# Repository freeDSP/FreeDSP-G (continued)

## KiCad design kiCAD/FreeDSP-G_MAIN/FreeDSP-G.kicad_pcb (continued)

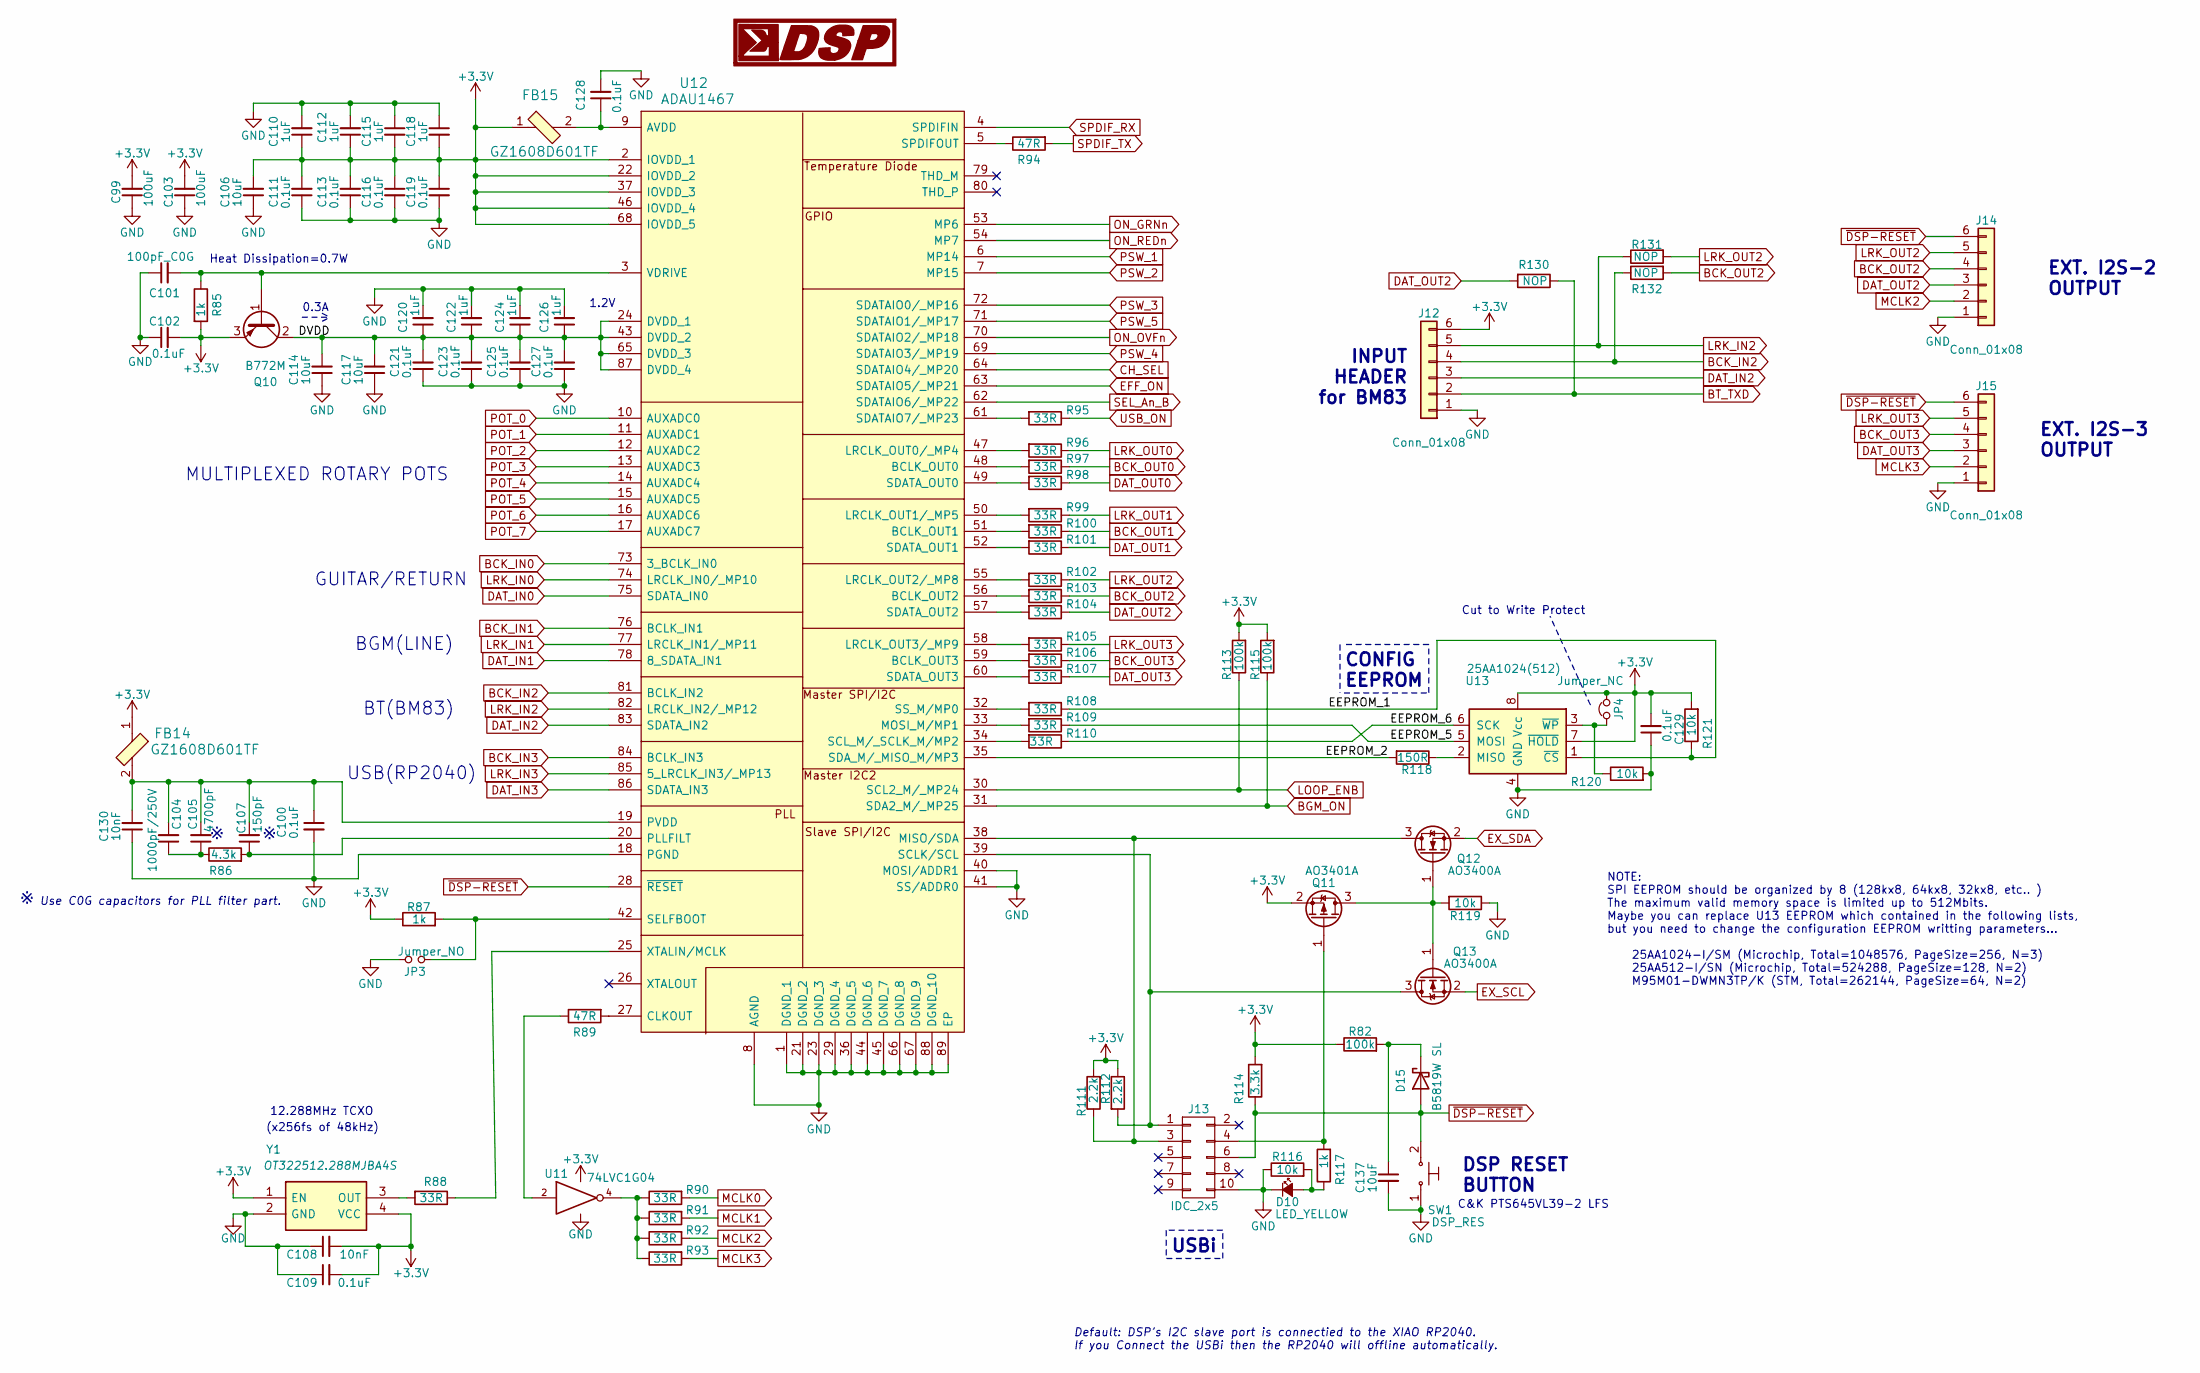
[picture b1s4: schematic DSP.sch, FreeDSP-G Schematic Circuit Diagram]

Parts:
C99, C103: 100uF; C_1206_3216Metric
C100, C102, C109, C111, C113, C116, C119, C121, C123, C125, C127, C128, C129: 0.1uF; C_0603_1608Metric_Pad1.08x0.95mm_HandSolder
C101: 100pF_C0G; C_0603_1608Metric_Pad1.08x0.95mm_HandSolder
C104: 1000pF/250V; C_0805_2012Metric
C105: 4700pF; C_0805_2012Metric
C106, C114, C117, C137: 10uF; C_0805_2012Metric
C107: 150pF; C_0805_2012Metric
C108, C130: 10nF; C_0603_1608Metric_Pad1.08x0.95mm_HandSolder
C110, C112, C115, C118, C120, C122, C124, C126: 1uF; C_0603_1608Metric_Pad1.08x0.95mm_HandSolder
D10: LED_YELLOW; LED_0603_1608Metric_Castellated
D15: B5819W SL; D_SOD-123
FB14, FB15: GZ1608D601TF; L_0603_1608Metric_Pad1.05x0.95mm_HandSolder; MPN BLM18AG601SN1D; Digi-Key_PN 490-1014-1-ND
J12, J14, J15: Conn_01x08; PinHeader_1x06_P2.54mm_Vertical
J13: IDC_2x5; IDC-Header_2x05_P2.54mm_Vertical
JP3: Jumper_NO; PinHeader_1x02_P2.54mm_Vertical
JP4: Jumper_NC; SolderJumper-2_P1.3mm_Bridged_RoundedPad1.0x1.5mm
Q10: B772M; TO-252-2
Q11: AO3401A; SOT-23; Manufacturer_Part_Number DMG3415U-7; Mouser Part Number 621-DMG3415U-7
Q12, Q13: AO3400A; SOT-23
R82, R113, R115: 100k; R_0603_1608Metric_Pad0.98x0.95mm_HandSolder
R85, R87, R117: 1k; R_0603_1608Metric_Pad0.98x0.95mm_HandSolder
R86: 4.3k; R_0603_1608Metric_Pad0.98x0.95mm_HandSolder
R88, R90, R91, R92, R93, R95, R96, R97, R98, R99, R100, R101, R102, R103, R104, R105, R106, R107, R108, R109, R110: 33R; R_0603_1608Metric_Pad0.98x0.95mm_HandSolder
R89, R94: 47R; R_0603_1608Metric_Pad0.98x0.95mm_HandSolder
R111, R112: 2.2k; R_0603_1608Metric_Pad0.98x0.95mm_HandSolder
R114: 3.3k; R_0603_1608Metric_Pad0.98x0.95mm_HandSolder
R116, R119, R120, R121: 10k; R_0603_1608Metric_Pad0.98x0.95mm_HandSolder
R118: 150R; R_0603_1608Metric_Pad0.98x0.95mm_HandSolder
R130, R131, R132: NOP; R_0603_1608Metric_Pad0.98x0.95mm_HandSolder
SW1: DSP_RES; SW_Tactile_SPST_Angled_PTS645Vx83-2LFS
U11: 74LVC1G04; SOT-23-5_HandSoldering
U12: ADAU1467; ADAU1467WBCPZ300
U13: 25AA1024(512); SOIC-8_3.9x4.9mm_P1.27mm
Y1: OT322512.288MJBA4S; Crystal_SMD_TXC_7M-4pin_3.2x2.5mm_HandSoldering; Manufacturer_Part_Number KC7050K50.0000C1GE00
Z1: LOGO; SigmaDSP-LogoSmall

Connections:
+3V3: C99.2, C102.2, C103.2, C106.2, C108.2, C109.2, C110.1, C111.2, C112.1, C113.2, C115.2, C116.1, C118.2, C119.1, C129.2, FB14.1, FB15.1, J12.6, JP4.2, Q10.3 (E), Q11.2 (S), R82.1, R85.2, R87.1, R111.2, R112.1, R113.2, R114.2, R115.2, R121.2, U11.5 (VCC), U12.2 (IOVDD_1), U12.22 (IOVDD_2), U12.37 (IOVDD_3), U12.46 (IOVDD_4), U12.68 (IOVDD_5), U13.7 (~HOLD), U13.8 (Vcc), Y1.1 (EN), Y1.4 (VCC); also elsewhere on the board
/DSP/DVDD: C114.2, C117.2, C120.1, C121.2, C122.1, C123.2, C124.1, C125.2, C126.1, C127.2, Q10.2 (C), U12.24 (DVDD_1), U12.43 (DVDD_2), U12.65 (DVDD_3), U12.87 (DVDD_4)
/DSP/EEPROM_1: R108.1, R121.1, U13.1 (~CS)
/DSP/EEPROM_2: R118.2, U12.35 (SDA_M/_MISO_M/MP3)
/DSP/EEPROM_5: R109.1, U13.5 (MOSI)
/DSP/EEPROM_6: R110.1, U13.6 (SCK)
BCK_IN0: U12.73 (3_BCLK_IN0); also elsewhere on the board
BCK_IN1: U12.76 (BCLK_IN1); also elsewhere on the board
BCK_IN2: J12.4, R132.1, U12.81 (BCLK_IN2); also elsewhere on the board
BCK_IN3: U12.84 (BCLK_IN3); also elsewhere on the board
BCK_OUT0: R97.1; also elsewhere on the board
BCK_OUT1: R100.1; also elsewhere on the board
BCK_OUT2: J14.4, R103.1, R132.2
BCK_OUT3: J15.4, R106.1
BGM_ON: R115.1, U12.31 (SDA2_M/_MP25); also elsewhere on the board
BT_TXD: J12.2, R130.1; also elsewhere on the board
CH_SEL: U12.64 (SDATAIO4/_MP20); also elsewhere on the board
DAT_IN0: U12.75 (SDATA_IN0); also elsewhere on the board
DAT_IN1: U12.78 (8_SDATA_IN1); also elsewhere on the board
DAT_IN2: J12.3, U12.83 (SDATA_IN2); also elsewhere on the board
DAT_IN3: U12.86 (SDATA_IN3); also elsewhere on the board
DAT_OUT0: R98.1; also elsewhere on the board
DAT_OUT1: R101.1; also elsewhere on the board
DAT_OUT2: J14.3, R104.1, R130.2
DAT_OUT3: J15.3, R107.1
EFF_ON: U12.63 (SDATAIO5/_MP21); also elsewhere on the board
EX_SCL: Q13.2 (S); also elsewhere on the board
EX_SDA: Q12.2 (S); also elsewhere on the board
GND: C99.1, C100.2, C101.1, C102.1, C103.1, C106.1, C108.1, C109.1, C110.2, C111.1, C112.2, C113.1, C114.1, C115.1, C116.2, C117.1, C118.1, C119.2, C120.2, C121.1, C122.2, C123.1, C124.2, C125.1, C126.2, C127.1, C128.2, C129.1, C130.1, C137.2, D10.1 (K), J12.1, J13.10, J14.1, J15.1, JP3.1, R116.1, R119.1, R120.2, SW1.1, U11.3 (GND), U12.1 (DGND_1), U12.8 (AGND), U12.18 (PGND), U12.21 (DGND_2), U12.23 (DGND_3), U12.29 (DGND_4), U12.36 (DGND_5), U12.40 (MOSI/ADDR1), U12.41 (SS/ADDR0), U12.44 (DGND_6), U12.45 (DGND_7), U12.66 (DGND_8), U12.67 (DGND_9), U12.88 (DGND_10), U12.89 (EP), U13.4 (GND), Y1.2 (GND); also elsewhere on the board
LOOP_ENB: R113.1, U12.30 (SCL2_M/_MP24); also elsewhere on the board
LRK_IN0: U12.74 (LRCLK_IN0/_MP10); also elsewhere on the board
LRK_IN1: U12.77 (LRCLK_IN1/_MP11); also elsewhere on the board
LRK_IN2: J12.5, R131.1, U12.82 (LRCLK_IN2/_MP12); also elsewhere on the board
LRK_IN3: U12.85 (5_LRCLK_IN3/_MP13); also elsewhere on the board
LRK_OUT0: R96.1; also elsewhere on the board
LRK_OUT1: R99.1; also elsewhere on the board
LRK_OUT2: J14.5, R102.1, R131.2
LRK_OUT3: J15.5, R105.1
MCLK0: R90.2; also elsewhere on the board
MCLK1: R91.2; also elsewhere on the board
MCLK2: J14.2, R92.2; also elsewhere on the board
MCLK3: J15.2, R93.2; also elsewhere on the board
unnamed: C100.1, C104.2, C105.2, C107.2, C130.2, FB14.2, U12.19 (PVDD)
unnamed: C101.2, Q10.1 (B), R85.1, U12.3 (VDRIVE)
unnamed: C104.1, C105.1, R86.1
unnamed: C107.1, R86.2, U12.20 (PLLFILT)
unnamed: C128.1, FB15.2, U12.9 (AVDD)
unnamed: C137.1, D15.1 (K), R82.2
unnamed: D10.2 (A), R116.2, R117.1
unnamed: J13.1, Q13.3 (D), R112.2, U12.39 (SCLK/SCL)
unnamed: J13.3, Q12.3 (D), R111.1, U12.38 (MISO/SDA)
unnamed: J13.4, Q11.1 (G), R117.2
unnamed: JP3.2, R87.2, U12.42 (SELFBOOT)
unnamed: JP4.1, R120.1, U13.3 (~WP)
unnamed: Q11.3 (D), Q12.1 (G), Q13.1 (G), R119.2
unnamed: R88.1, U12.25 (XTALIN/MCLK)
unnamed: R88.2, Y1.3 (OUT)
unnamed: R89.1, U11.2
unnamed: R89.2, U12.27 (CLKOUT)
unnamed: R90.1, R91.1, R92.1, R93.1, U11.4
unnamed: R94.1, U12.5 (SPDIFOUT)
unnamed: R95.2, U12.61 (SDATAIO7/_MP23)
unnamed: R96.2, U12.47 (LRCLK_OUT0/_MP4)
unnamed: R97.2, U12.48 (BCLK_OUT0)
unnamed: R98.2, U12.49 (SDATA_OUT0)
unnamed: R99.2, U12.50 (LRCLK_OUT1/_MP5)
unnamed: R100.2, U12.51 (BCLK_OUT1)
unnamed: R101.2, U12.52 (SDATA_OUT1)
unnamed: R102.2, U12.55 (LRCLK_OUT2/_MP8)
unnamed: R103.2, U12.56 (BCLK_OUT2)
unnamed: R104.2, U12.57 (SDATA_OUT2)
unnamed: R105.2, U12.58 (LRCLK_OUT3/_MP9)
unnamed: R106.2, U12.59 (BCLK_OUT3)
unnamed: R107.2, U12.60 (SDATA_OUT3)
unnamed: R108.2, U12.32 (SS_M/MP0)
unnamed: R109.2, U12.33 (MOSI_M/MP1)
unnamed: R110.2, U12.34 (SCL_M/_SCLK_M/MP2)
unnamed: R118.1, U13.2 (MISO)
ON_GRNn: U12.53 (MP6); also elsewhere on the board
ON_OVFn: U12.70 (SDATAIO2/_MP18); also elsewhere on the board
ON_REDn: U12.54 (MP7); also elsewhere on the board
POT_0: U12.10 (AUXADC0); also elsewhere on the board
POT_1: U12.11 (AUXADC1); also elsewhere on the board
POT_2: U12.12 (AUXADC2); also elsewhere on the board
POT_3: U12.13 (AUXADC3); also elsewhere on the board
POT_4: U12.14 (AUXADC4); also elsewhere on the board
POT_5: U12.15 (AUXADC5); also elsewhere on the board
POT_6: U12.16 (AUXADC6); also elsewhere on the board
POT_7: U12.17 (AUXADC7); also elsewhere on the board
PSW_1: U12.6 (MP14); also elsewhere on the board
PSW_2: U12.7 (MP15); also elsewhere on the board
PSW_3: U12.72 (SDATAIO0/_MP16); also elsewhere on the board
PSW_4: U12.69 (SDATAIO3/_MP19); also elsewhere on the board
PSW_5: U12.71 (SDATAIO1/_MP17); also elsewhere on the board
SEL_An_B: U12.62 (SDATAIO6/_MP22); also elsewhere on the board
SPDIF_RX: U12.4 (SPDIFIN); also elsewhere on the board
SPDIF_TX: R94.2; also elsewhere on the board
USB_ON: R95.1; also elsewhere on the board
~DSP-RESET: D15.2 (A), J13.6, J14.6, J15.6, R114.1, SW1.2, U12.28 (~RESET)

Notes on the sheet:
USBi
12.288MHz TCXO
USB(RP2040)
GUITAR/RETURN
MULTIPLEXED ROTARY POTS
BGM(LINE)
(x256fs of 48kHz)
NOTE: SPI EEPROM should be organized by 8 (128kx8, 64kx8, 32kx8, etc.. ) The maximum valid memory space is limited up to 512Mbits. Maybe you can replace U13 EEPROM which contained in the following lists, but you need to change the configuration EEPROM writting parameters… 25AA1024-I/SM (Microchip, 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
Default: DSP’s I2C slave port is connectied to the XIAO RP2040. If you Connect the USBi then the RP2040 will offline automatically.
0.3A
1.2V
Heat Dissipation=0.7W
DSP RESET BUTTON
C&K PTS645VL39-2 LFS
BT(BM83)
Cut to Write Protect
CONFIG EEPROM
Use C0G capacitors for PLL filter part.
INPUT HEADER for BM83
EXT. I2S-2 OUTPUT
EXT. I2S-3 OUTPUT

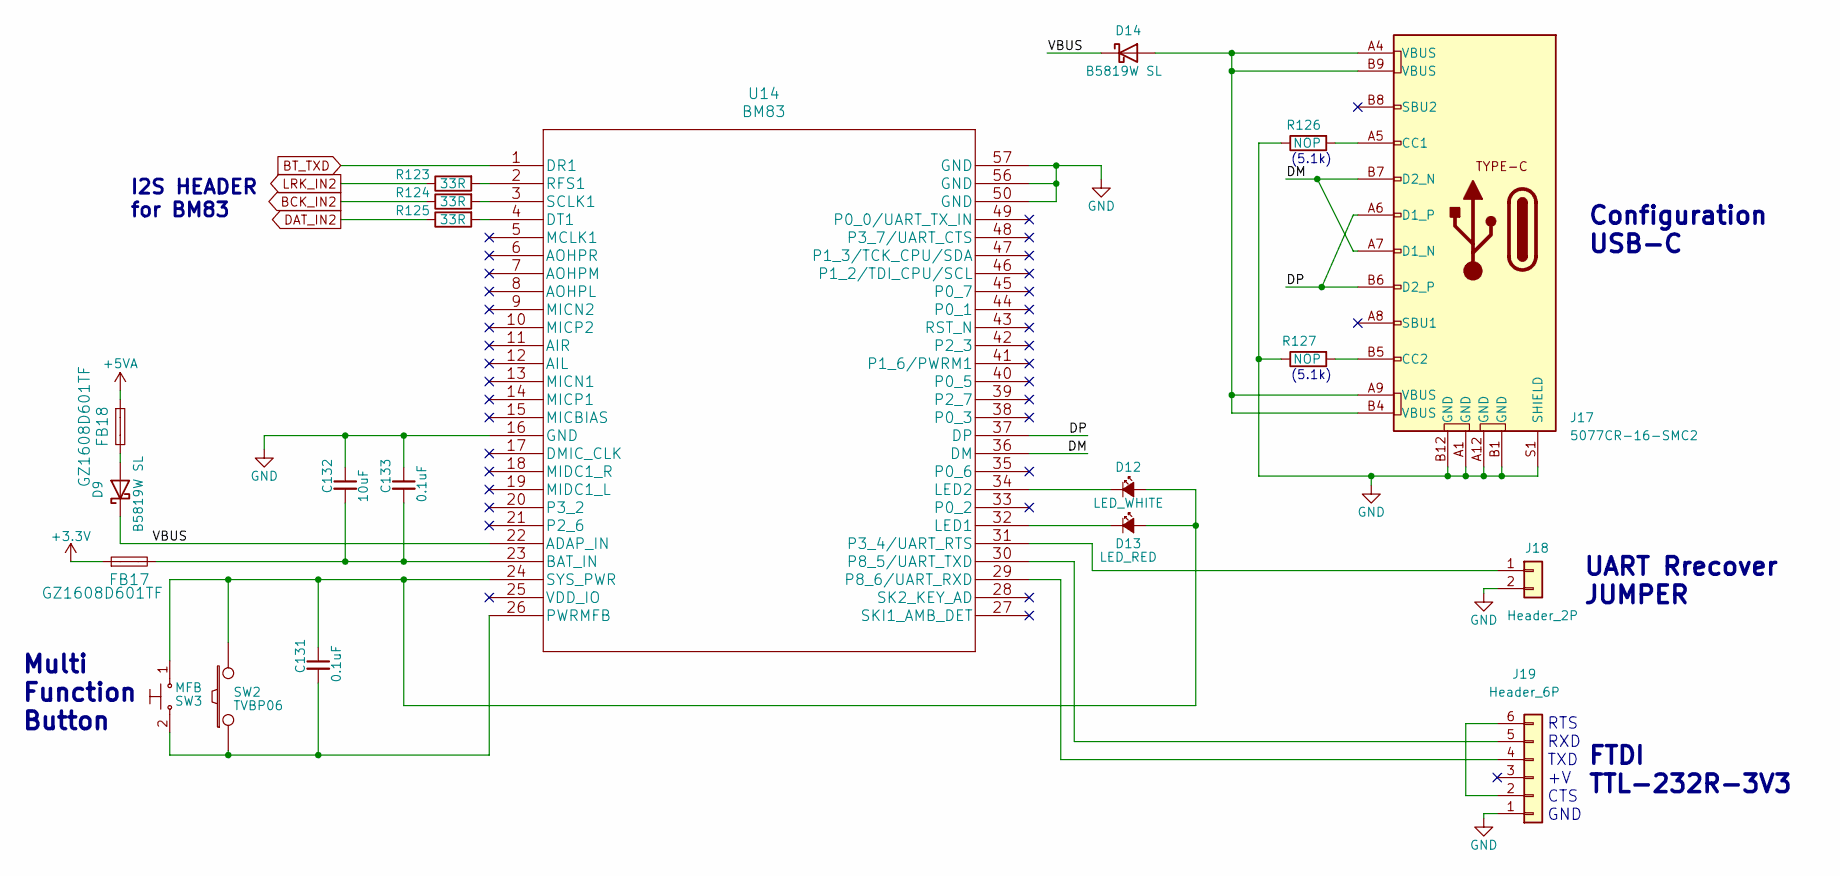
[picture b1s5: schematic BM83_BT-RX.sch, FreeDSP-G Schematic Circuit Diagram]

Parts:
C131, C133: 0.1uF; C_0603_1608Metric_Pad1.08x0.95mm_HandSolder
C132: 10uF; C_0805_2012Metric
D9, D14: B5819W SL; D_SOD-123
D12: LED_WHITE; LED_0603_1608Metric_Castellated
D13: LED_RED; LED_0603_1608Metric_Castellated
FB17, FB18: GZ1608D601TF; L_0603_1608Metric_Pad1.05x0.95mm_HandSolder; MPN BLM18AG601SN1D; Digi-Key_PN 490-1014-1-ND
J17: 5077CR-16-SMC2; USB-C_5077CR-16-SMC2-BK-TR
J18: Header_2P; PinHeader_1x02_P2.54mm_Vertical
J19: Header_6P; PinHeader_1x06_P2.54mm_Vertical
R123, R124, R125: 33R; R_0603_1608Metric_Pad0.98x0.95mm_HandSolder
R126, R127: NOP; R_0603_1608Metric_Pad0.98x0.95mm_HandSolder
SW2: TVBP06; MJTP1250
SW3: MFB; SW_Tactile_SPST_Angled_PTS645Vx83-2LFS
U14: BM83; BM83_MCH

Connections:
+3V3: FB17.1; also elsewhere on the board
+5VA: FB18.1; also elsewhere on the board
/BM83_BT-RX/DM: J17.A7 (D1_N), J17.B7 (D2_N), U14.36 (DM)
/BM83_BT-RX/DP: J17.A6 (D1_P), J17.B6 (D2_P), U14.37 (DP)
/BM83_BT-RX/VBUS: D9.1 (K), D14.1 (K), U14.22 (ADAP_IN)
BCK_IN2: R124.1; also elsewhere on the board
BT_TXD: U14.1 (DR1); also elsewhere on the board
DAT_IN2: R125.1; also elsewhere on the board
GND: C132.1, C133.1, J17.A1 (GND), J17.A12 (GND), J17.B1 (GND), J17.B12 (GND), J17.S1 (SHIELD), J18.2, J19.1, R126.1, R127.1, U14.16 (GND), U14.50 (GND), U14.56 (GND), U14.57 (GND); also elsewhere on the board
LRK_IN2: R123.1; also elsewhere on the board
unnamed: C131.1, D12.2 (A), D13.2 (A), SW2.2, SW3.1, U14.24 (SYS_PWR)
unnamed: C131.2, SW2.1, SW3.2, U14.26 (PWRMFB)
unnamed: C132.2, C133.2, FB17.2, U14.23 (BAT_IN)
unnamed: D9.2 (A), FB18.2
unnamed: D12.1 (K), U14.34 (LED2)
unnamed: D13.1 (K), U14.32 (LED1)
unnamed: D14.2 (A), J17.A4 (VBUS), J17.A9 (VBUS), J17.B4 (VBUS), J17.B9 (VBUS)
unnamed: J17.A5 (CC1), R126.2
unnamed: J17.B5 (CC2), R127.2
unnamed: J18.1, U14.31 (P3_4/UART_RTS)
unnamed: J19.2, J19.6
unnamed: J19.4, U14.29 (P8_6/UART_RXD)
unnamed: J19.5, U14.30 (P8_5/UART_TXD)
unnamed: R123.2, U14.2 (RFS1)
unnamed: R124.2, U14.3 (SCLK1)
unnamed: R125.2, U14.4 (DT1)

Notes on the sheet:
I2S HEADER for BM83
RTS RXD TXD +V CTS GND
FTDI TTL-232R-3V3
UART Rrecover JUMPER
Configuration USB-C
Multi Function Button
(5.1k)

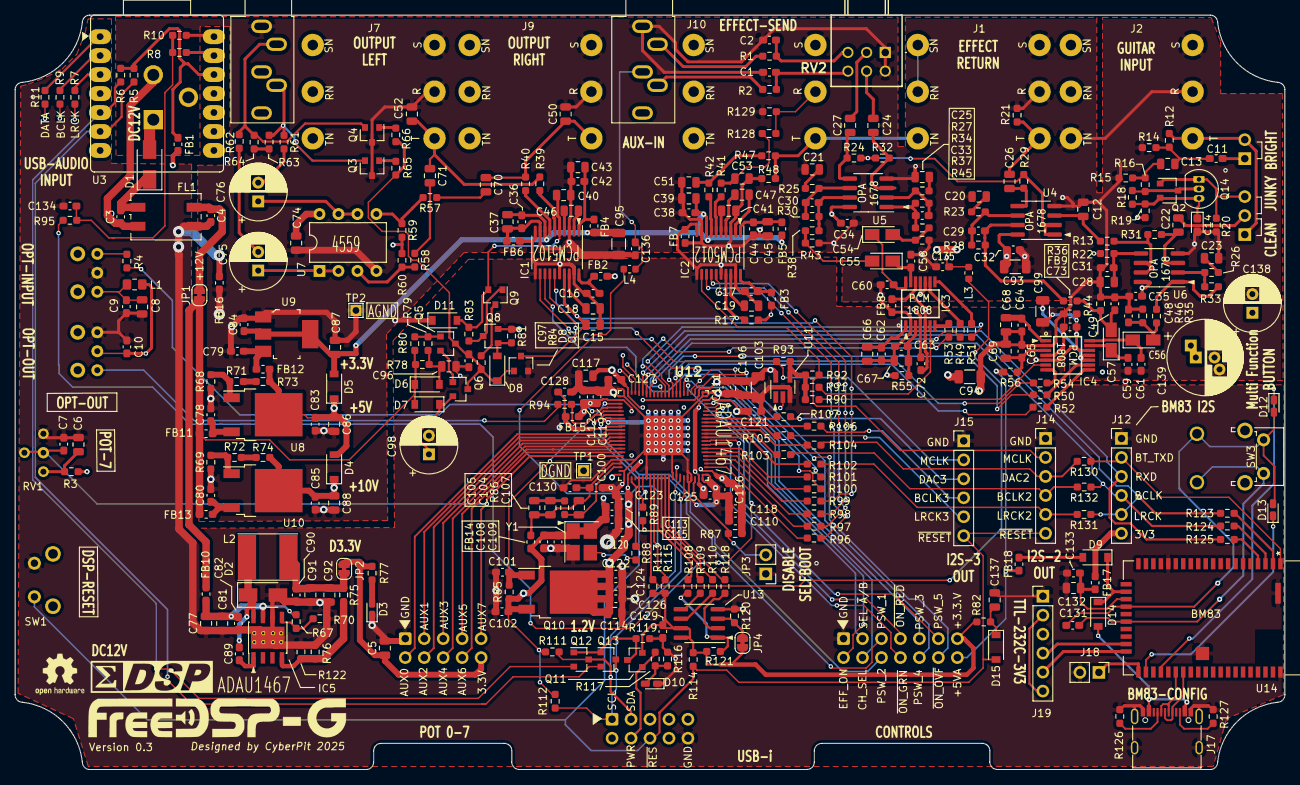
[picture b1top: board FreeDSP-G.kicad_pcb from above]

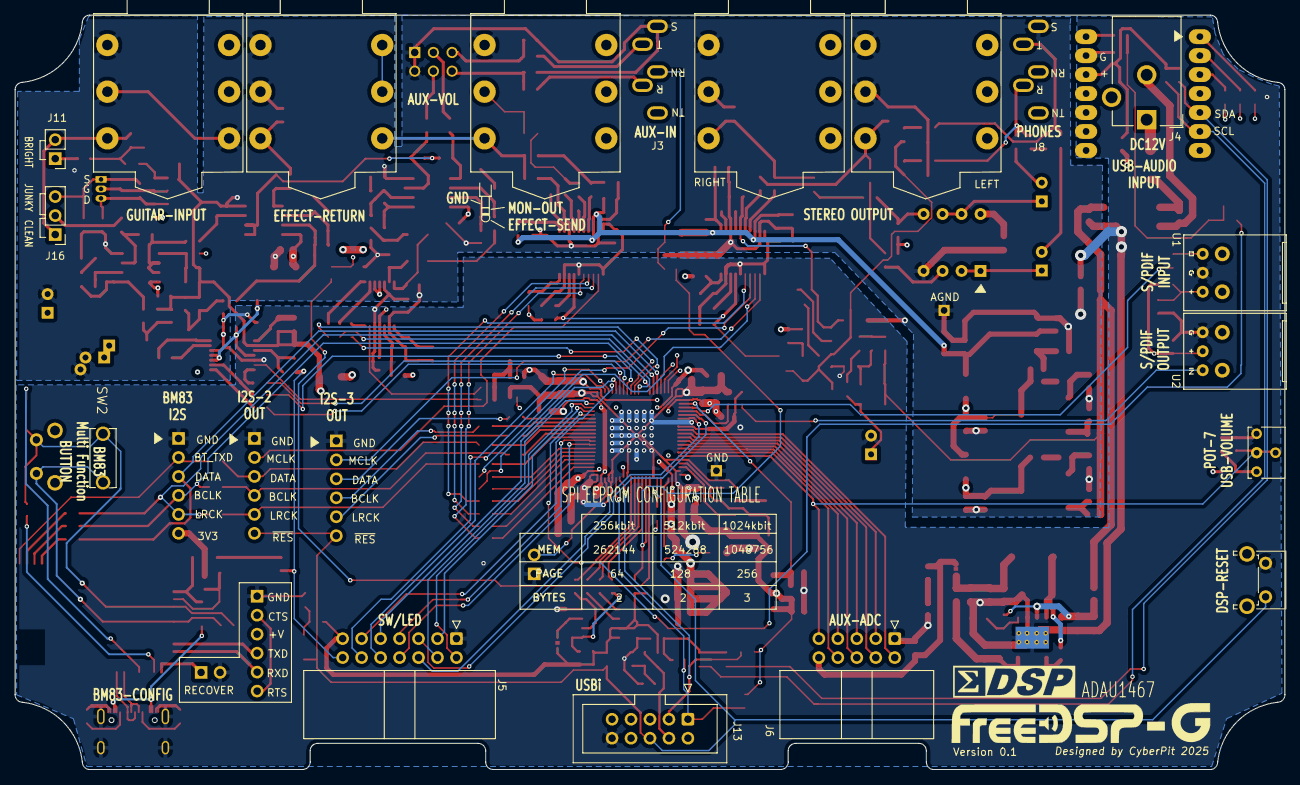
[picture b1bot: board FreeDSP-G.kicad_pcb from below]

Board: 4 copper layers, 170.0 x 101.0 mm, 374 parts (16 on the bottom side), 247 nets.

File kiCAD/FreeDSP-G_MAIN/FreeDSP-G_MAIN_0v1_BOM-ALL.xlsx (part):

Reference(s) | Qty | JLPCB# | Value | Footprint | Description | Datasheet
IC5 | 1 | C9864 | TPS5430DDA | Package_SO:TI_SO-PowerPAD-8_ThermalVias | SMPS for digital part | http://www.ti.com/lit/ds/symlink/tps5430.pdf
C93 | 1 | C96123 | 47uF/10V | Capacitor_SMD:C_1206_3216Metric |  | ~
D4, D5, D7, D8, D9, D11 | 6 | C8598 | B5819W SL | Diode_SMD:D_SOD-123 | SBD 1A/40V | http://www.vishay.com/docs/85660/bat42.pdf
Q5, Q6 | 2 | C8326 | MMBT5401 | Package_TO_SOT_SMD:SOT-23 | PNP Transistor 350mW | ~
R72 | 1 | C8218 | 200R | Resistor_SMD:R_0603_1608Metric_Pad0.98x0.95mm_HandSolder |  | ~
D6 | 1 | C81598 | 1N4148W | Diode_SMD:D_SOD-123 | Switching Diode 150mA/75V | ~
Q3, Q4 | 2 | C79973 | 2SD2704KT146 | Package_TO_SOT_SMD:SOT-23 | NPN Transistor for anti-pop muting | ~
U8, U10 | 2 | C75510 | LM317AG-TN3-R | Package_TO_SOT_SMD:TO-252-2 | Voltage Regurator for Analog | https://datasheet.lcsc.com/lcsc/2304140030_UTC-Unisonic-Tech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
D10 | 1 | C72038 | LED_YELLOW | LED_SMD:LED_0603_1608Metric_Castellated | Indicator for USBi is Active
C54, C55, C56, C57 | 4 | C7171 | 10uF/16V(Ta) | Capacitors_Tantalum_SMD:CP_Tantalum_Case-A_EIA-3216-18_Reflow | Tanatalium 3216 metric
U12 | 1 | C654414 | ADAU1467 | Myfootprints:ADAU1467WBCPZ300 | SigmaDSP | https://www.analog.com/media/en/technical-documentation/data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
U9 | 1 | C6186 | AMS1117-3.3 | digikey-footprints:SOT-223
C108, C130 | 2 | C57112 | 10nF | Capacitor_SMD:C_0603_1608Metric_Pad1.08x0.95mm_HandSolder |  | ~
IC3, IC4 | 2 | C55513 | PCM1808QPWR | Myfootprints:PCM1808QPWRQ1 | ADC 99dB SNR @48kHz Sampling | http://www.ti.com/lit/ds/symlink/pcm1808-q1.pdf
C5, C8, C37, C39, C43, C45, C69, C106, C114, C117, C132 | 11 | C440198 | 10uF | Capacitor_SMD:C_0805_2012Metric |  | ~
C6, C66, C67, C68 | 4 | C440198 | 10uF | Capacitor_SMD:C_0805_2012Metric
C14, C21, C25, C28 | 4 | C440198 | 10uF | Capacitor_SMD:C_0805_2012Metric |  | ~
C15, C18, C19, C40, C41, C46, C47, C70, C71, C74 | 10 | C440198 | 10uF | Capacitor_SMD:C_0805_2012Metric
C77, C96 | 2 | C440198 | 10uF/50V | Capacitor_SMD:C_0805_2012Metric | for the Power-ON delay timing | ~
U11 | 1 | C434067 | 74LVC1G04 | Package_TO_SOT_SMD:SOT-23-5_HandSoldering | for Coax S/PDIF Input Amp | http://www.ti.com/lit/sg/scyt129e/scyt129e.pdf
R5, R6, R20, R111, R112 | 5 | C4190 | 2.2k | Resistor_SMD:R_0603_1608Metric_Pad0.98x0.95mm_HandSolder |  | ~
R10 | 1 | C4177 | 1.8k | Resistor_SMD:R_0603_1608Metric_Pad0.98x0.95mm_HandSolder |  | ~
C50, C51, C52, C53, C104 | 5 | C343010 | 1000pF/250V | Capacitor_SMD:C_0805_2012Metric | C0G PLL Loop FIlter Snabber Cap | ~
Q10 | 1 | C33027 | B772M | Package_TO_SOT_SMD:TO-252-2 | PNP 1.25W 3A Transistor for 1.2V Power Rail | ~
R17 | 1 | C31850 | 22k | Resistor_SMD:R_0603_1608Metric_Pad0.98x0.95mm_HandSolder
R18 | 1 | C31850 | 10MEG | Resistor_SMD:R_0603_1608Metric_Pad0.98x0.95mm_HandSolder
R65, R66 | 2 | C31850 | 22k | Resistor_SMD:R_0603_1608Metric_Pad0.98x0.95mm_HandSolder |  | ~
Q2 | 1 | C2999170 | 2SK208GR | TO_SOT_Packages_SMD:SC-59 | Replace of 2SK30A | ~
Q14 | 1 | C2999170 | 2SK30A-GR | TO_SOT_Packages_THT:TO-92_Inline_Narrow_Oval | Replace of 2SK30A | ~
FL1 | 1 | C2981417 | MACM9070-701 | Myfootprints:ACM9070 | TDK - ACM9070-701-2PL-TL01 - FILTER, COMMON MODE, 5A, SMD | http://www.mouser.com/ds/2/400/e9713_acm-16715.pdf
Y1 | 1 | C2896602 | OT322512.288MJBA4S | Crystals:Crystal_SMD_TXC_7M-4pin_3.2x2.5mm_HandSoldering | 24.576MHz or 22.5792MHz TCXO 1.6 to 3.63 Volts | http://www.kyocera.co.jp/prdct/electro/pdf/clock_k_j.pdf
C12, C20, C22, C24, C26, C27 | 6 | C28323 | 1uF | Capacitor_SMD:C_0805_2012Metric |  | ~
C81 | 1 | C28323 | 1uF/50V | Capacitor_SMD:C_0805_2012Metric |  | ~
C86, C87, C88 | 3 | C28323 | 1uF | Capacitor_SMD:C_0805_2012Metric |  | ~
C13 | 1 | C28233 | 100nF | Capacitor_SMD:C_0805_2012Metric |  | ~
R28, R30, R34, R36, R37, R38, R84 | 7 | C25819 | 47k | Resistor_SMD:R_0603_1608Metric_Pad0.98x0.95mm_HandSolder |  | ~
R1, R2 | 2 | C25810 | 18k | Resistor_SMD:R_0603_1608Metric_Pad0.98x0.95mm_HandSolder
R16, R77, R82, R116, R119, R120, R121 | 7 | C25804 | 10k | Resistor_SMD:R_0603_1608Metric_Pad0.98x0.95mm_HandSolder |  | ~
R13, R21, R22, R24, R29, R31, R32, R57, R58, R59, R60, R79, R113, R115 | 14 | C25803 | 100k | Resistor_SMD:R_0603_1608Metric_Pad0.98x0.95mm_HandSolder |  | ~
R69 | 1 | C23228 | 680R | Resistor_SMD:R_0603_1608Metric_Pad0.98x0.95mm_HandSolder |  | ~
R19 | 1 | C23212 | 6.8k | Resistor_SMD:R_0603_1608Metric_Pad0.98x0.95mm_HandSolder |  | ~
R75 | 1 | C23189 | 5.6k | Resistor_SMD:R_0603_1608Metric_Pad0.98x0.95mm_HandSolder
R49, R50, R51, R52, R53, R54, R89, R94 | 8 | C23182 | 47R | Resistor_SMD:R_0603_1608Metric_Pad0.98x0.95mm_HandSolder
R12, R78 | 2 | C23178 | 470K | Resistor_SMD:R_0603_1608Metric_Pad0.98x0.95mm_HandSolder
R23, R25, R27 | 3 | C23162 | 4.7k | Resistor_SMD:R_0603_1608Metric_Pad0.98x0.95mm_HandSolder |  | ~
R86 | 1 | C23159 | 4.3k | Resistor_SMD:R_0603_1608Metric_Pad0.98x0.95mm_HandSolder |  | ~
R7, R9, R11, R61, R62, R88, R90, R91, R92, R93, R95, R96, R97, R98, R99, R100, 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 | 29 | C23140 | 33R | Resistor_SMD:R_0603_1608Metric_Pad0.98x0.95mm_HandSolder |  | ~
R68 | 1 | C23138 | 330R | Resistor_SMD:R_0603_1608Metric_Pad0.98x0.95mm_HandSolder |  | ~
R8, R70, R76 | 3 | C22978 | 3.3k | Resistor_SMD:R_0603_1608Metric_Pad0.98x0.95mm_HandSolder |  | ~
R43, R44, R45, R46 | 4 | C22967 | 27k | Resistor_SMD:R_0603_1608Metric_Pad0.98x0.95mm_HandSolder
R39, R40, R41, R42 | 4 | C22962 | 220R | Resistor_SMD:R_0603_1608Metric_Pad0.98x0.95mm_HandSolder
R14, R15, R80, R81, R83 | 5 | C22935 | 1MEG | Resistor_SMD:R_0603_1608Metric_Pad0.98x0.95mm_HandSolder |  | ~
D3, D12 | 2 | C2290 | LED_WHITE | LED_SMD:LED_0603_1608Metric_Castellated | Remove this if you use LED extension header
D13 | 1 | C2286 | LED_RED | LED_SMD:LED_0603_1608Metric_Castellated | Remove this if you use LED extension header
R55, R56, R73 | 3 | C22859 | 10R | Resistor_SMD:R_0603_1608Metric_Pad0.98x0.95mm_HandSolder |  | ~
R48, R129 | 2 | C22828 | 180R | Resistor_SMD:R_0603_1608Metric_Pad0.98x0.95mm_HandSolder |  | ~
R122 | 1 | C22827 | 180k | Resistor_SMD:R_0603_1608Metric_Pad0.98x0.95mm_HandSolder
R67 | 1 | C22809 | 15k | Resistor_SMD:R_0603_1608Metric_Pad0.98x0.95mm_HandSolder |  | ~
R118 | 1 | C22808 | 150R | Resistor_SMD:R_0603_1608Metric_Pad0.98x0.95mm_HandSolder |  | ~
R35 | 1 | C22790 | 12k | Resistor_SMD:R_0603_1608Metric_Pad0.98x0.95mm_HandSolder
R3, R63, R64, R71 | 4 | C22775 | 100R | Resistor_SMD:R_0603_1608Metric_Pad0.98x0.95mm_HandSolder |  | ~
D1 | 1 | C22452 | D_Schottky_5A | Diode_SMD:D_SMA | SBD 40V 550mV@5A | ~
D2 | 1 | C22452 | D_Schottky_5A | Diode_SMD:D_SMA | SBD 40V 550mV@5A | ~
U13 | 1 | C219767 | 25AA1024(512) | Package_SO:SOIC-8_3.9x4.9mm_P1.27mm | Might be substitute with 256Mbit/512Mbit SPI EEPROM | http://ww1.microchip.com/downloads/en/DeviceDoc/21832H.pdf
R47, R85, R87, R117, R128 | 5 | C21190 | 1k | Resistor_SMD:R_0603_1608Metric_Pad0.98x0.95mm_HandSolder |  | ~
R4, R33, R74, R114 | 4 | C21189 | 0R | Resistor_SMD:R_0603_1608Metric_Pad0.98x0.95mm_HandSolder | Chip Jumper | ~
Q1 | 1 | C20917 | AO3400A | TO_SOT_Packages_SMD:SOT-23 | N Ch MOSFET | https://www.fairchildsemi.com/datasheets/2N/2N7002.pdf
Q7, Q9, Q12, Q13 | 4 | C20917 | AO3400A | Package_TO_SOT_SMD:SOT-23 | MOSFET N-CH 60V 115MA SOT-23 | https://www.onsemi.com/pub/Collateral/NDS7002A-D.PDF
U4, U5, U6 | 3 | C192421 | OPA1678IDR | Package_SO:SOIC-8_5.275x5.275mm_P1.27mm | Dual Op-Amp | http://www.ti.com/lit/ds/symlink/opa1678.pdf
L2 | 1 | C177244 | 22uH(2.5A) | Inductor_SMD:L_Taiyo-Yuden_NR-60xx_HandSoldering | Metal-Alloy Power Inductor Rated 2.5A 7x6.6mm
C105 | 1 | C1744 | 4700pF | Capacitor_SMD:C_0805_2012Metric | PLL Loop FIlter Cap (C0G will better) | ~
C107 | 1 | C1716 | 150pF | Capacitor_SMD:C_0805_2012Metric | PLL Loop FIlter Cap (C0G will better) | ~
C91, C92 | 2 | C16780 | 47uF/6.3V | Capacitor_SMD:C_0805_2012Metric | for Negative SMPS Power Integration | ~
C11 | 1 | C1620 | 470pF | Capacitor_SMD:C_0603_1608Metric_Pad1.08x0.95mm_HandSolder |  | ~
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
